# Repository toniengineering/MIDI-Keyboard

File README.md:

So for half life week three I'm building the tutorial project which is a MIDI Keyboard. I plan on giving it to my friend afterwards as a gift. For my keyboard I'm making a pcb and a 3d printable case. I'm useing the esp32s2 with a SN74AHCT125N and ads1115 for more IO pins. I added 5 touch keys which are piano keys, I did one encoder and two sliders with five swtiches and an LED for each switch. For my case I ended going with an open case because it's all I could manage at the moment but I think the case still turned out nice. And the pcb will screw into it.
[MIDI Keyboard.csv](https://github.com/user-attachments/files/33945325/MIDI.Keyboard.csv)"Reference","Qty","Value","DNP","Exclude from BOM","Exclude from Board","Footprint","Datasheet"
"D1,D3,D6,D9,D10","5","SK6812MINI-E","","","","LED_SMD:LED_SK6812MINI-E_3.2x2.8mm_P1.5mm_ReverseMount","https://www.lcsc.com/datasheet/C5149201.pdf"
"D2,D4,D5,D7,D8","5","D","","","","Diode_SMD:D_SOD-123",""
"D11,D12","2","1N5819","","","","Diode_THT:D_DO-41_SOD81_P10.16mm_Horizontal","http://www.vishay.com/docs/88525/1n5817.pdf"
"J1","1","Conn_01x05","","","","mtpr:Untitled",""
"J2","1","Barrel_Jack_MountingPin","","","","Connector_BarrelJack:BarrelJack_Horizontal",""
"RV1,RV2","2","Slider","","","","Potentiometer_THT:Potentiometer_Bourns_PTA1543_Single_Slide",""
"SW1","1","RotaryEncoder_Switch_MP","","","","Rotary_Encoder:RotaryEncoder_Alps_EC11E-Switch_Vertical_H20mm",""
"SW2,SW3,SW4,SW5,SW6","5","SW_Push","","","","mtpr:Kailh Choc Low-Profile Switches",""
"U1","1","XIAO-ESP32-S3-DIP","","","","mtpr:XIAO ESP32-S3",""
"U2","1","ADS1115IDGS","","","","Package_SO:TSSOP-10_3x3mm_P0.5mm","http://www.ti.com/lit/ds/symlink/ads1113.pdf"
"U3","1","SN74AHCT125N","","","","mtpr:DIP794W45P254L1930H508Q14",""

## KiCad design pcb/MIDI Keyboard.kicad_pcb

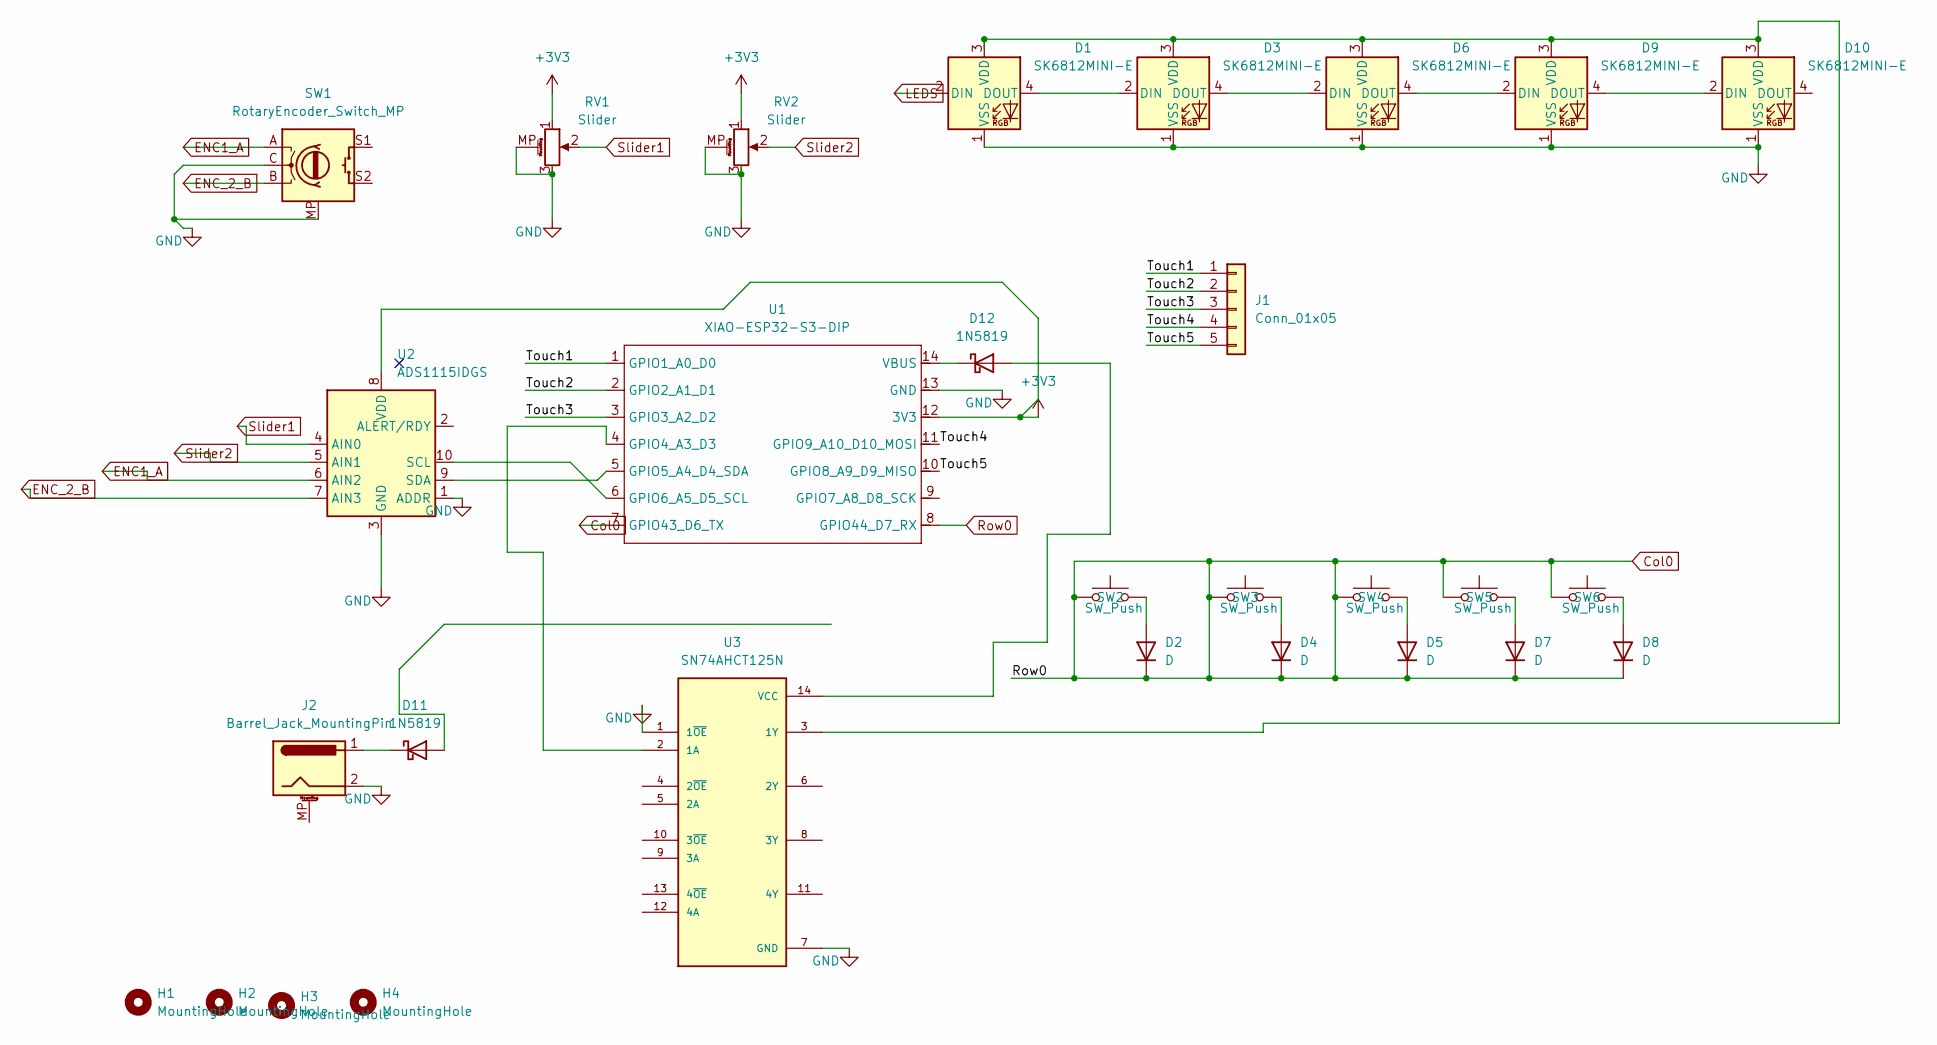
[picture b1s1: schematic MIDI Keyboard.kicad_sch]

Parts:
D1, D3, D6, D9, D10: SK6812MINI-E; LED_SK6812MINI-E_3.2x2.8mm_P1.5mm_ReverseMount
D2, D4, D5, D7, D8: D; D_SOD-123
D11, D12: 1N5819; D_DO-41_SOD81_P10.16mm_Horizontal
H1, H2, H3, H4: MountingHole; MountingHole_2.5mm
J1: Conn_01x05; Untitled
J2: Barrel_Jack_MountingPin; BarrelJack_Horizontal
RV1, RV2: Slider; Potentiometer_Bourns_PTA1543_Single_Slide
SW1: RotaryEncoder_Switch_MP; RotaryEncoder_Alps_EC11E-Switch_Vertical_H20mm
SW2, SW3, SW4, SW5, SW6: SW_Push; Kailh Choc Low-Profile Switches
U1: XIAO-ESP32-S3-DIP; XIAO ESP32-S3
U2: ADS1115IDGS; TSSOP-10_3x3mm_P0.5mm
U3: SN74AHCT125N; DIP794W45P254L1930H508Q14; PARTREV Q

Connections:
+3V3: RV1.1, RV2.1, U1.12 (3V3), U2.8 (VDD)
/Touch1: J1.1, U1.1 (GPIO1_A0_D0)
/Touch2: J1.2, U1.2 (GPIO2_A1_D1)
/Touch3: J1.3, U1.3 (GPIO3_A2_D2)
/Touch4: J1.4, U1.11 (GPIO9_A10_D10_MOSI)
/Touch5: J1.5, U1.10 (GPIO8_A9_D9_MISO)
Col0: D2.1 (K), D4.1 (K), D5.1 (K), D7.1 (K), D8.1 (K), SW2.1, SW3.1, SW4.1, SW5.1, SW6.1, U1.7 (GPIO43_D6_TX), U1.8 (GPIO44_D7_RX)
ENC1_A: SW1.A, U2.6 (AIN2)
ENC_2_B: SW1.B, U2.7 (AIN3)
GND: D1.1 (VSS), D3.1 (VSS), D6.1 (VSS), D9.1 (VSS), D10.1 (VSS), J2.2, RV1.3, RV1.MP (MountPin), RV2.3, RV2.MP (MountPin), SW1.C, SW1.MP, U1.13 (GND), U2.1 (ADDR), U2.3 (GND), U3.1 (1~OE), U3.7 (GND)
LEDS: D1.2 (DIN)
unnamed: D1.4 (DOUT), D3.2 (DIN)
unnamed: D1.3 (VDD), D3.3 (VDD), D6.3 (VDD), D9.3 (VDD), D10.3 (VDD), U3.3 (1Y)
unnamed: D2.2 (A), SW2.2
unnamed: D3.4 (DOUT), D6.2 (DIN)
unnamed: D4.2 (A), SW3.2
unnamed: D5.2 (A), SW4.2
unnamed: D6.4 (DOUT), D9.2 (DIN)
unnamed: D7.2 (A), SW5.2
unnamed: D8.2 (A), SW6.2
unnamed: D9.4 (DOUT), D10.2 (DIN)
unnamed: D11.1 (K_1), J2.1
unnamed: D12.2 (A), U3.14 (VCC)
unnamed: D12.1 (K), U1.14 (VBUS)
unnamed: U1.4 (GPIO4_A3_D3), U3.2 (1A)
unnamed: U1.5 (GPIO5_A4_D4_SDA), U2.9 (SDA)
unnamed: U1.6 (GPIO6_A5_D5_SCL), U2.10 (SCL)
Slider1: RV1.2, U2.4 (AIN0)
Slider2: RV2.2, U2.5 (AIN1)

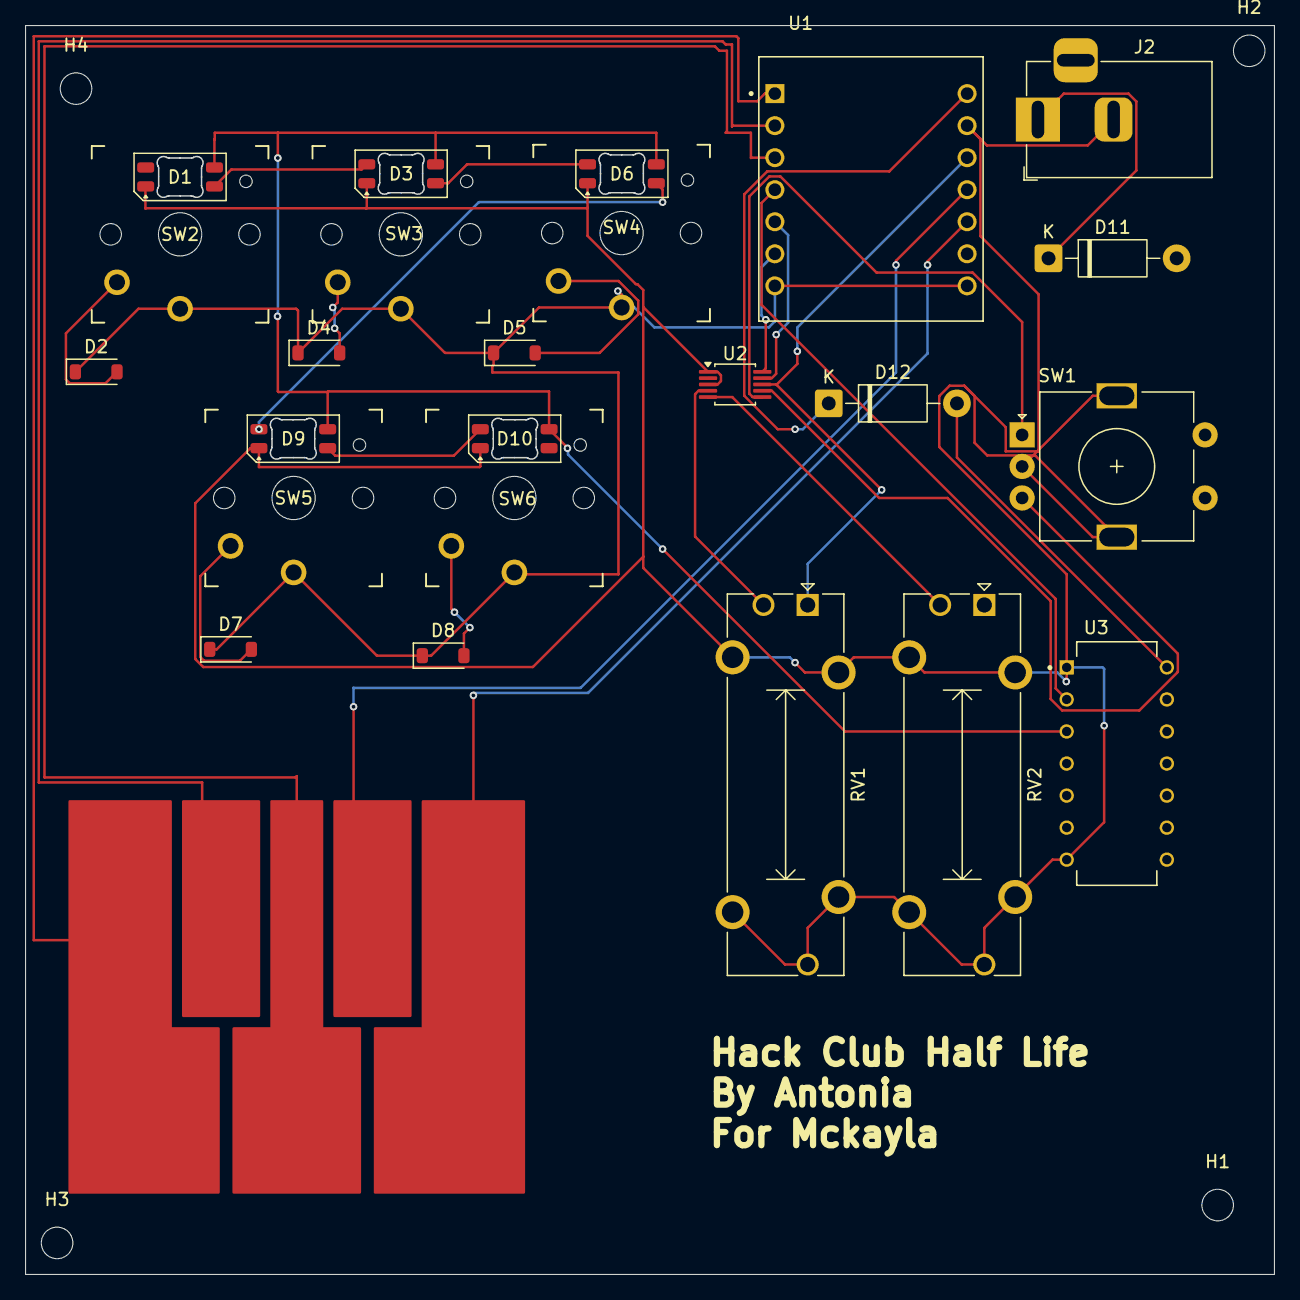
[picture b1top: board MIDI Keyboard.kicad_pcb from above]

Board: 2 copper layers, 99.0 x 99.0 mm, 29 parts (0 on the bottom side), 28 nets.
